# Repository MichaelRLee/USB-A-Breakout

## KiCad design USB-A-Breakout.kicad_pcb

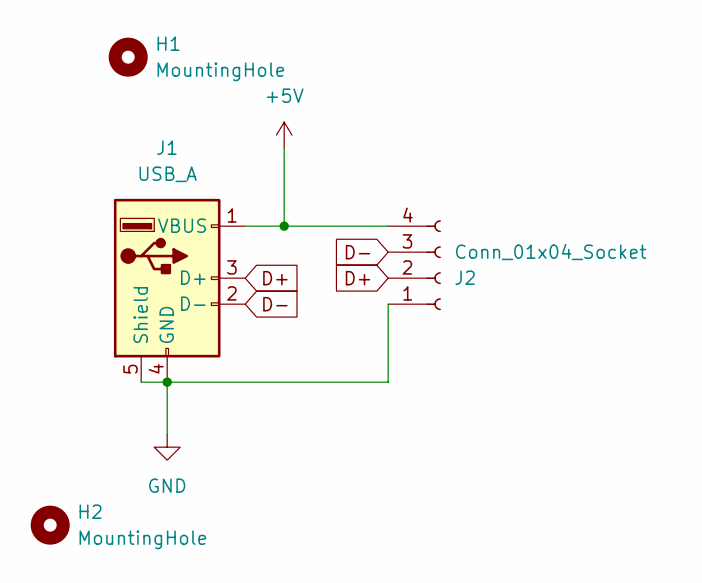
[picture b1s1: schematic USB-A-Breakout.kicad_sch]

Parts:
H1, H2: MountingHole; MountingHole_3.2mm_M3_Pad
J1: USB_A; USB-A-TH_AF-ZJB13.7
J2: Conn_01x04_Socket; PinHeader_1x04_P2.54mm_Vertical

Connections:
+5V: J1.1 (VBUS), J2.4
D+: J1.3 (D+), J2.2
D-: J1.2 (D-), J2.3
GND: J1.4 (GND), J1.5 (Shield), J2.1

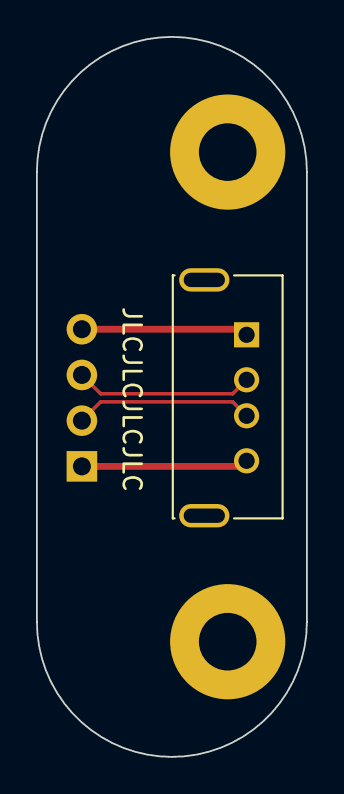
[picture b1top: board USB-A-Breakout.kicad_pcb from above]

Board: 2 copper layers, 15.0 x 40.0 mm, 4 parts (1 on the bottom side), 4 nets.

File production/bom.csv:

Designator,Footprint,Quantity,Value,LCSC Part #
J1,USB-A-TH_AF-ZJB13.7,1,USB_A,
J2,PinHeader_1x04_P2.54mm_Vertical,1,Conn_01x04_Socket,

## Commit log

2025-05-06 Version 1
2025-05-06 Draft done
2025-05-07 Revised footprint
